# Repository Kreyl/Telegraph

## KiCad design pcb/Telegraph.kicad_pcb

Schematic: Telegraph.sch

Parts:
BZ1: BUZZER; BUZZER_HC0903
C1, C2, C3, C4: 10n; CAP_0603
C7, C21, C32, C34: 10u; CAP_0805
C8, C9, C11, C12, C14, C15, C16, C20, C26, C27, C28, C29, C51: 0.1u; CAP_0603
C10, C13: 20pF; CAP_0603
C17: 1000u; CAP_10xxR
C18: 1000pF; CAP_0603
C19: 1u; CAP_0603
C22, C23, C24, C25, C30, C31: 100p; CAP_0603
C33, C35: 4u7/63v; CAP_0805
C36, C38: 220n/16v; CAP_0603
C37, C39: 10n/50v; CAP_0603
C40, C41, C42, C43, C44, C45, C46, C47: 0.1u/50v; CAP_0603
C48, C49: 100u/63v; CAP_10xxR
C50: 4u7; CAP_0805
D1, D2: SMBJ15CA; SMB_DO214AA
D3, D4, D5, D6, D7, D9, D10, D15, D16, D17, D27: LED; LED_Through-Hole-3mm
D13, D14: SS14; SMA_DO214AC
D18, D19, D20, D21, D22: LED; LED_0603
D23, D24, D25, D26: 1N4148; SOD80C
DA1: LP2951; SO8
DA2: IPS6041; SO8HEATSINK
DD1: STM32F405RX-64; LQFP64
HOLE1, HOLE2, HOLE3, HOLE4, HOLE5, HOLE6, HOLE8, HOLE9, HOLE10: HOLE_METALLED; Hole3_5_out6mm
L1: BLM; IND_0402
Q1, Q2, Q6, Q7, Q10, Q11: BC848; SOT23-3
Q5: DVIUC6-4SC6; SOT23-6
Q14: MMBT2222; SOT23-3
R1, R6, R69, R71: 4k7; RES_0603
R3, R4, R7, R47, R48, R49, R72: 200; RES_0603
R9, R10, R13, R14, R18, R19, R50, R53, R54, R66, R67: 1k; RES_0603
R17: 1M; RES_0603
R22, R23, R26, R28, R34, R35, R42, R43, R55, R73: 10k; RES_0603
R27, R29: 150; RES_0603
R38, R39, R51: 20k; RES_0603
R46: 200R; RES_0603
R52: 12k; RES_0603
R56, R57, R58, R59: 510R; RES_0603
R60, R61, R62, R63, R64, R65: 39K; RES_0603
R68, R70: 33k; RES_0603
R74: 330k; RES_0603
R75: 100k; RES_0603
SW1: DIPx4; DIP_SMD_X4
SW2: SWITCH_H; SW_SS9
SW3: BUTTON; BTN_6x6
SW4, SW5: SWITCH_2x; BTN_PSM6
TP1, TP2, TP3, TP4, TP5, TP6, TP7, TP8, TP9, TP10, TP11, TP12, TP13, TP14: TESTPOINT; TESTPOINT_1MM
U1, U2: L6470; HTSSOP28
VCap1, VCap2: 2.2u; CAP_0603
XL1, XL2: CONN_2; SPRING_TERM_XY124V_A_2
XL5: CONN_3; PLS-3
XL6: ST_SWD; PLS-4
XL7: USB_MICRO_B; USBmicro_MOLEX_WM17142
XL8: BARREL_SOCKET; Barrel
XL9, XL16: CONN_2; TermiBlockHeader_508_x2_R
XL10, XL11, XL12, XL13, XL14: CONN_2; PLS-2
XL15: CONN_5; PLS-5
XL17, XL18: CONN_4; TermiBlockHeader_508_x4_R
XTAL1: 12 MHz; 0503x4-4

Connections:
+3.3V: BZ1.2, C7.1, C8.1, C9.1, C11.1, C12.1, C15.1, C18.1, C19.1, C50.1, DA1.1, DD1.1 (VBAT), DD1.19 (VDD), DD1.32 (VDD), DD1.48 (VDD), DD1.64 (VDD), L1.2, R26.1, R28.1, R42.1, R43.1, R51.1, SW3.2, XL6.1 (Vdd)
+12V: C16.1, C17.1, C20.1, C21.1, C36.2, C38.2, C40.1, C41.1, C42.1, C43.1, C44.1, C45.1, C46.1, C47.1, C48.1, C49.1, D25.A, D26.A, DA1.8, DA2.5, DA2.6, DA2.7, DA2.8, R13.1, R14.1, R66.1, R68.1, R70.1, SW2.1, U1.2 (VSA), U1.12 (VSB), U1.16 (VSB), U1.26 (VSA), U2.2 (VSA), U2.12 (VSB), U2.16 (VSB), U2.26 (VSA)
/5V_USB: C2.2, Q5.5 (Vbus), R53.2, XL7.1 (UVcc)
/ADC_1: R68.2, R69.1, U1.5 (ADC_IN)
/ADC_2: R70.2, R71.1, U2.5 (ADC_IN)
/BUSY/SYNC_1: C22.1, D20.C, DD1.8 ((ADC123-10)/PC0), R60.2, TP1.1, U1.22 (BUSY\SYNC)
/BUSY/SYNC_2: C23.1, D21.C, DD1.11 ((ADC123-13)/MOSI2/PC3), R61.2, TP4.1, U2.22 (BUSY\SYNC)
/BatteryMeas: C51.1, DD1.26 (PB0/T3C3/(ADC12-8)), R74.1, R75.2
/Buzzer: DD1.55 (PB3/SCK3/T2C2/SCK1), R67.2
/BuzzerOut: BZ1.1, Q14.3 (C)
/D+: DD1.45 (OTGFS_DP/PA12), Q5.3 (IO2), Q5.4 (IO3), XL7.3 (D+)
/D-: DD1.44 (OTGFS_DM/T1C4/PA11), Q5.1 (IO1), Q5.6 (IO4), XL7.2 (D-)
/DBG_UART_RX: DD1.59 (PB7/SDA1/T4C2/RX1), XL5.3
/DBG_UART_TX: DD1.58 (PB6/SCL1/T4C1/TX1), XL5.2 (PM)
/DS1: DD1.29 (PB10/SCK2/SCL2/TX3/T2C3), SW1.8
/DS2: DD1.30 (PB11/SDA2/RX3/T2C4), SW1.7
/DS3: DD1.38 (T8C2/RX6/T3C2/SDIO_D7/PC7), SW1.6
/DS4: DD1.39 (T8C3/T3C3/CK6/SDIO_D0/PC8), SW1.5
/FLAG_1: C24.1, D18.C, DD1.10 ((ADC123-12)/MISO2/PC2), R62.2, TP3.1, U1.24 (FLAG)
/FLAG_2: C25.1, D19.C, DD1.25 ((ADC12-15)/PC5), R63.2, TP6.1, U2.24 (FLAG)
/GPIO1: DD1.40 (MCO2/T8C4/SDA3/T3C4/SDIO_D1/PC9), XL11.1
/GPIO2: DD1.51 (SCK3/TX4/TX3/SDIO_D2/PC10), XL12.1
/GPIO3: DD1.52 (MISO3/RX4/RX3/SDIO_D3/PC11), XL13.1
/GPIO4: DD1.53 (MOSI3/TX5/CK3/SDIO_CK/PC12), XL14.1
/LED1: DD1.16 ((ADC123-2)/T5C3/T9C1/T2C3/TX2/PA2), R47.1
/LED2: DD1.17 ((ADC123-3)/T5C4/T9C2/T2C4/RX2/PA3), R48.1
/LED3: DD1.50 (PA15), R49.1
/LED4: DD1.2 (PC13), R72.1
/LED_BT_LOW: DD1.28 (PB2/BOOT1), R4.1
/LED_BT_PWR: DD1.27 (PB1/T3C4/(ADC12-9)), R3.1
/LED_SRC_PWR: DD1.4 ((OC32OUT)/PC15), R7.1
/LineIn1: D1.A, SW4.2, SW4.5, XL1.1
/LineIn2: D2.A, SW5.2, SW5.5, XL2.1
/LineTx1: DD1.56 (PB4/MISO3/T3C1/MISO1), R9.2
/LineTx2: DD1.57 (PB5/MOSI3/T3C2/MOSI1), R10.2
/MOTOR_CS: DD1.41 (MCO1/SCL3/T1C1/CK1/PA8), TP11.1, U1.23 (CS), U2.23 (CS)
/MOTOR_MISO: DD1.22 ((ADC12-6)/T13C1/T3C1/MISO1/PA6), TP14.1, U2.18 (SDO)
/MOTOR_MOSI: DD1.23 ((ADC12-7)/T14C1/T3C2/MOSI1/PA7), TP13.1, U1.20 (SDI)
/MOTOR_SCK: DD1.21 ((ADC12-5)/(DAC2)/SCK1/PA5), TP12.1, U1.19 (CK), U2.19 (CK)
/MagnetIN: DD1.43 (OTGFS_ID/T1C3/RX1/PA10), R55.1
/MagnetOUT: DA2.4, XL16.1
/OUT1_1A: U1.1 (OUT1A), XL17.2 (PM)
/OUT1_1B: U1.14 (OUT1B), XL17.3
/OUT1_2A: U1.28 (OUT2A), XL17.1
/OUT1_2B: U1.15 (OUT2B), XL17.4
/OUT2_1A: U2.1 (OUT1A), XL18.2 (PM)
/OUT2_1B: U2.14 (OUT1B), XL18.3
/OUT2_2A: U2.28 (OUT2A), XL18.1
/OUT2_2B: U2.15 (OUT2B), XL18.4
/PWR_BAT: D14.A, R74.2, XL9.1
/PWR_IN: D13.C, D14.C, SW2.2
/PWR_SRC: D13.A, R73.1, XL8.PWR
/PwrSrcSns: DD1.3 ((OC32IN)/PC14), R73.2
/RSL1: DD1.33 (PB12/CK3), XL15.1
/RSL2: DD1.34 (PB13/SCK2), XL15.2
/RSL3: DD1.35 (PB14/MISO2/T12C1), XL15.3
/RSL4: DD1.36 (PB15/MOSI2/T12C2), XL15.4
/SDI_2: TP9.1, U1.18 (SDO), U2.20 (SDI)
/SHLD: C1.1, R17.1, XL7.SHLD
/STBY/RST: C30.1, C31.1, DD1.37 (T8C1/TX6/T3C1/SDIO_D6/PC6), R64.2, R65.2, TP10.1, U1.3 (STBY\RST), U2.3 (STBY\RST)
/STEP_CLK_1: DD1.61 (PB8/SDIO_D4/T4C3/T10C1/SCL1), TP7.1, U1.25 (STCK)
/STEP_CLK_2: DD1.62 (PB9/SDIO_D5/T4C4/T11C1/SDA1), TP8.1, U2.25 (STCK)
/SWCLK: DD1.49 (SWCLK/(PA14)), XL6.2 (SWCLK)
/SWDIO: DD1.46 (SWDIO/(PA13)), XL6.4 (SWDIO)
/SW_1: DD1.9 ((ADC123-11)/PC1), TP2.1, U1.4 (SW)
/SW_2: DD1.24 ((ADC12-14)/PC4), TP5.1, U2.4 (SW)
/TrgOut1: DD1.14 ((ADC123-0)/TX4/T5C1/WKUP/PA0), Q10.3 (C), R42.2
/TrgOut2: DD1.15 ((ADC123-1)/RX4/T5C2/T2C2/PA1), Q11.3 (C), R43.2
/Vdd1: C26.1, C27.1, C32.1, C33.1, R56.1, R58.1, R60.1, R62.1, R64.1, U1.6 (VREG), U1.17 (VDD)
/Vdd2: C28.1, C29.1, C34.1, C35.1, R57.1, R59.1, R61.1, R63.1, R65.1, U2.6 (VREG), U2.17 (VDD)
GND: C1.2, C2.1, C3.2, C4.2, C7.2, C8.2, C9.2, C10.2, C11.2, C12.2, C13.2, C14.2, C15.2, C16.2, C17.2, C19.2, C20.2, C21.2, C22.2, C23.2, C24.2, C25.2, C26.2, C27.2, C28.2, C29.2, C30.2, C31.2, C32.2, C33.2, C34.2, C35.2, C40.2, C41.2, C42.2, C43.2, C44.2, C45.2, C46.2, C47.2, C48.2, C49.2, C50.2, C51.2, D1.C, D2.C, D3.C, D4.C, D5.C, D6.C, D7.C, D9.A, D10.A, D15.C, D16.C, D17.C, D27.C, DA1.3, DA1.4, DA2.1, DD1.12 (VSSA), DD1.18 (VSS), DD1.63 (VSS), HOLE1.H, HOLE2.H, HOLE3.H, HOLE4.H, HOLE5.H, HOLE6.H, HOLE8.H, HOLE9.H, HOLE10.H, Q1.2 (E), Q2.2 (E), Q5.2 (GND), Q14.2 (E), R17.2, R22.2, R23.2, R27.2, R29.2, R38.2, R39.2, R50.2, R52.2, R69.2, R71.2, R75.1, SW1.1, SW1.2, SW1.3, SW1.4, SW2.H, U1.9 (AGND), U1.13 (PGND), U1.21 (DGND), U1.27 (PGND), U1.PAD, U2.9 (AGND), U2.13 (PGND), U2.21 (DGND), U2.27 (PGND), U2.PAD, VCap1.2, VCap2.2, XL1.2 (PM), XL2.2 (PM), XL5.1, XL6.3 (GND), XL7.4 (UGND), XL7.5 (UID), XL8.GND, XL9.2 (PM), XL10.2 (PM), XL11.2 (PM), XL12.2 (PM), XL13.2 (PM), XL14.2 (PM), XL15.5, XL16.2 (PM), XTAL1.H
unnamed: C3.1, Q6.1 (B), R18.2, R22.1
unnamed: C4.1, Q7.1 (B), R19.2, R23.1
unnamed: C10.1, DD1.5 (PH0/OSCIN), XTAL1.1
unnamed: C13.1, R46.2, XTAL1.2
unnamed: C14.1, DD1.13 (VDDA), L1.1
unnamed: C18.2, DA1.7, R51.2, R52.1
unnamed: C36.1, D23.C, U1.11 (VBOOT)
unnamed: C37.1, D23.A, D25.C
unnamed: C37.2, U1.10 (CP)
unnamed: C38.1, D24.C, U2.11 (VBOOT)
unnamed: C39.1, D24.A, D26.C
unnamed: C39.2, U2.10 (CP)
unnamed: D3.A, R3.2
unnamed: D4.A, R4.2
unnamed: D5.A, D9.C, R1.2
unnamed: D7.A, R7.2
unnamed: D6.A, D10.C, R6.2
unnamed: D15.A, R47.2
unnamed: D16.A, R48.2
unnamed: D17.A, R49.2
unnamed: D18.A, R56.2
unnamed: D19.A, R57.2
unnamed: D20.A, R58.2
unnamed: D21.A, R59.2
unnamed: D22.A, R66.2
unnamed: D22.C, DA2.3
unnamed: D27.A, R72.2
unnamed: DA2.2, R55.2
unnamed: DD1.6 (PH1/OSCOUT), R46.1
unnamed: DD1.20 ((ADC12-4)/(DAC1)/CK2/PA4), R54.1
unnamed: DD1.31 (VCap1), VCap1.1
unnamed: DD1.42 ((OTGFS_VBUS)/T1C2/TX1/PA9), R53.1
unnamed: DD1.47 (VCap2), VCap2.1
unnamed: DD1.60 (BOOT0), R50.1, SW3.1
unnamed: Q1.1 (B), R9.1
unnamed: Q1.3 (C), R13.2, R18.1, SW4.1, SW4.6
unnamed: Q2.1 (B), R10.1
unnamed: Q2.3 (C), R14.2, R19.1, SW5.1, SW5.6
unnamed: Q6.3 (C), R26.2, R34.1
unnamed: Q7.3 (C), R28.2, R35.1
unnamed: Q10.1 (B), R34.2, R38.1
unnamed: Q6.2 (E), Q10.2 (E), R27.1
unnamed: Q11.1 (B), R35.2, R39.1
unnamed: Q7.2 (E), Q11.2 (E), R29.1
unnamed: Q14.1 (B), R67.1
unnamed: R1.1, SW4.3, SW4.4
unnamed: R6.1, SW5.3, SW5.4
unnamed: R54.2, XL10.1

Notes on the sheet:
Line 1
Yellow
Red
Line 2
MOTOR DRIVER ICs
Lines
USB connect detector
SWD Programming
Debug UART
Key
Buzzer
Periphery UART1 (PB6, PB7) = Debug UART TIM1 C3 = MagnetIN TIM2 C2 = Buzzer TIM3 C1,C2 = LineTx1...4 TIM10 C1 = STEP_CLK_1 TIM11 C1 = STEP_CLK_2 ADC 0,1 (PA0,PA1) = line inputs ADC 8 (PB0) = Battery measurement
Rotary Switch
Maybe Limiters
Battery Pwr
Battery Low
Source Pwr

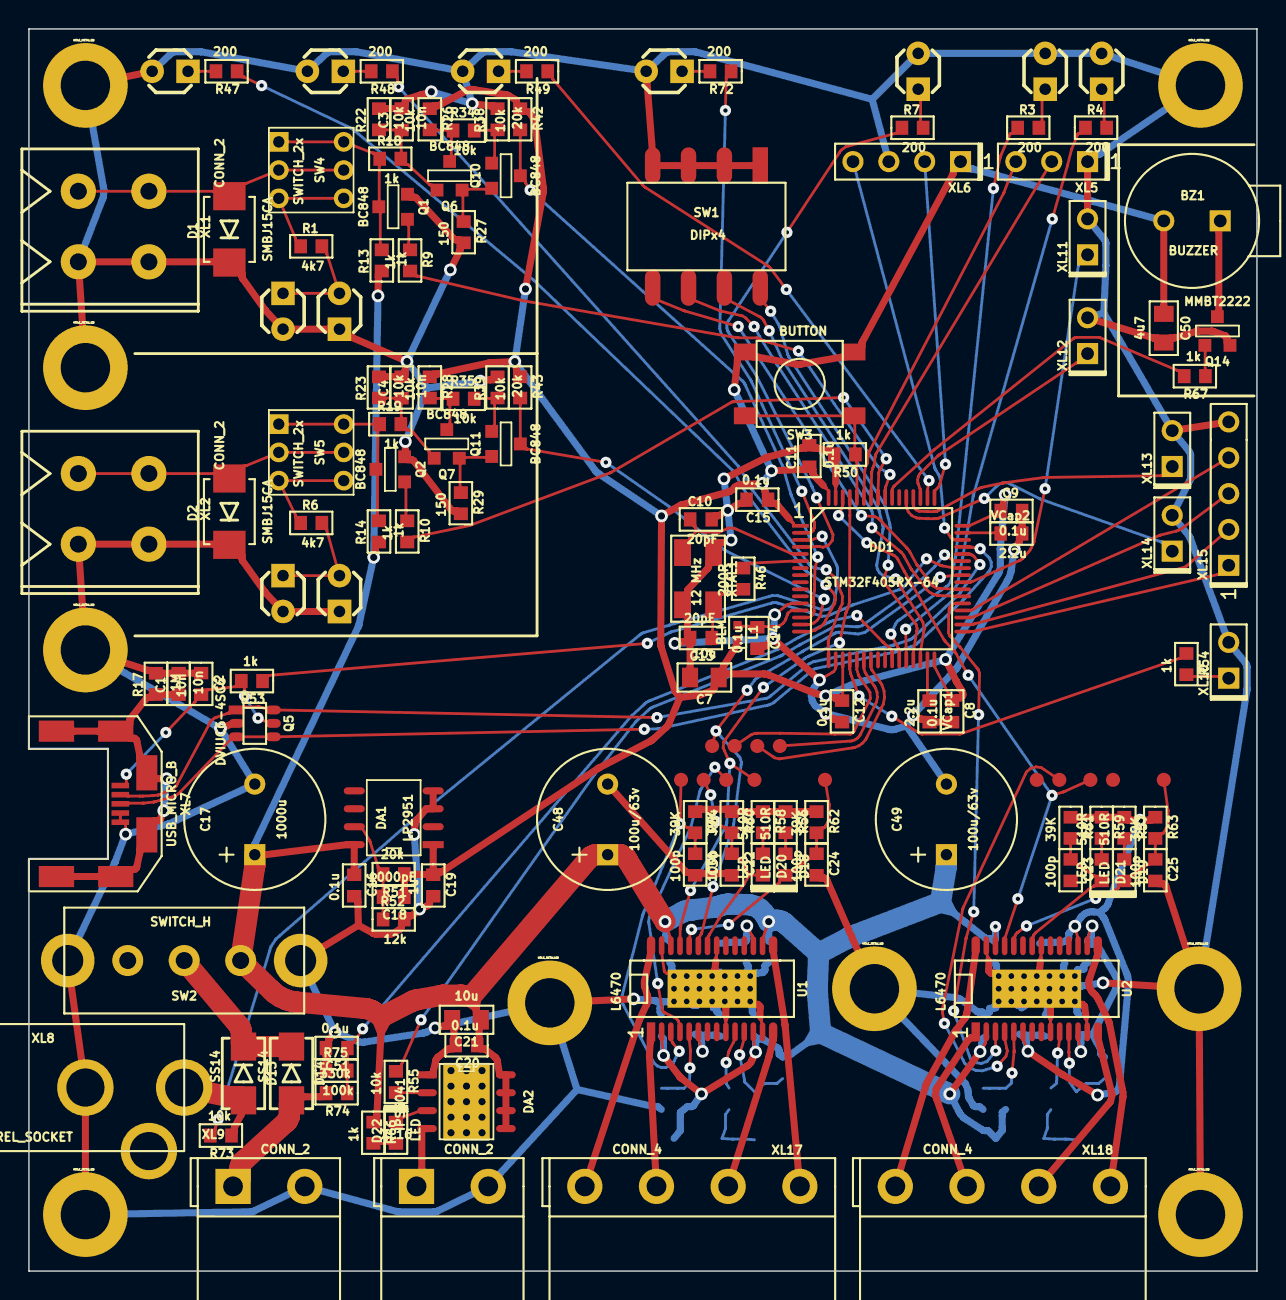
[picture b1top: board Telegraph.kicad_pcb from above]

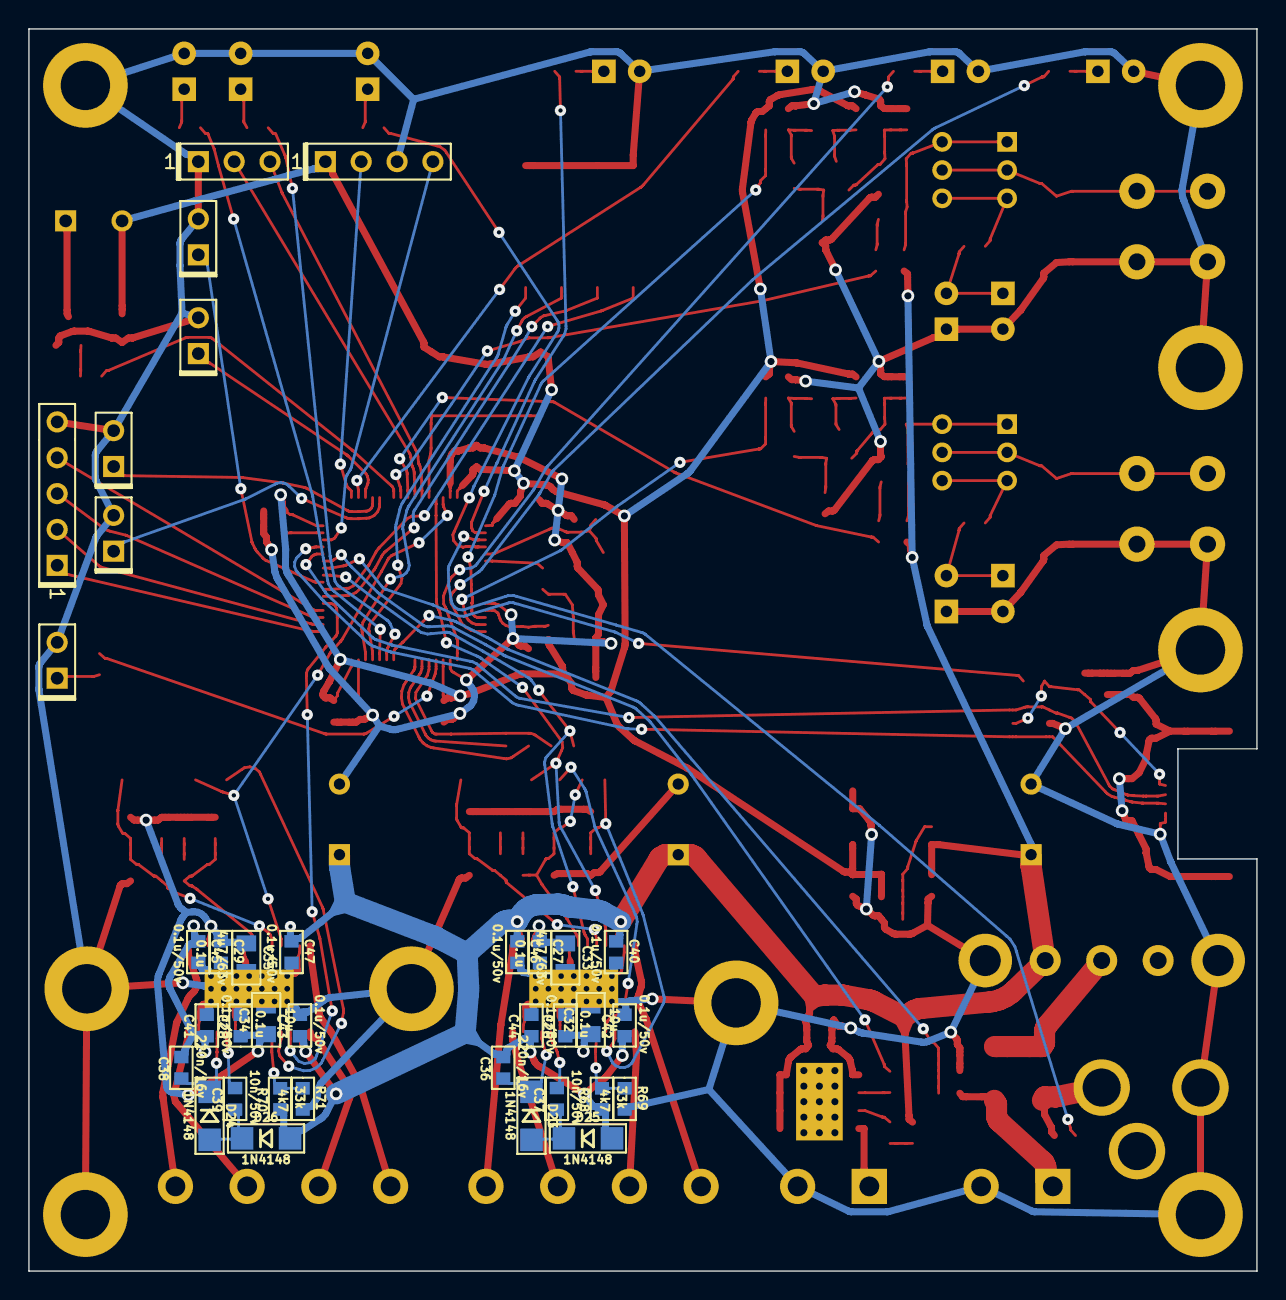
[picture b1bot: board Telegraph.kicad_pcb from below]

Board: 2 copper layers, 87.0 x 88.0 mm, 187 parts (28 on the bottom side), 119 nets.

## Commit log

2015-07-15 Sch in progress
2015-07-15 Proceeding with pcb
2015-07-16 Pcb routing started
2015-07-16 Proceeding
2015-07-17 PCB sent to production
2015-07-22 + Firmware: UART printf
2015-07-23 + USB Uart works
2015-07-23 + USB reporting
2015-07-23 + Beeper + Timers multipliers added to Clk_t: multiplier depends on APB divider.
2015-07-24 + USB 2 Beeper
2015-07-25 * switch to STM32f205xC ldscript * There is some bug in USB Uart
2015-07-25 + First motor run
2015-07-25 + Acceleration/deceleration + Key-based start/stop
2015-07-26 key & motor move in sync.
2015-07-26 - USB - Rx buffer Everything simplified
2015-07-26 + Periodic timer
2015-08-05 1905 Release
